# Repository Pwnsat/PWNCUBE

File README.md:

# PWNCUBE - The Vulnerable Satellite Hacking Platform for Learning Through Research

**A hardware-based CubeSat platform for aerospace cybersecurity research and training**, developed by PWNSAT in partnership with [ElectronicCats](https://github.com/ElectronicCats). PWNCUBE is a satellite design and vulnerability set onto real dual-core flight-computer hardware (Rockchip RV1106 — Cortex-A7 Linux + RISC-V RT-Thread), demonstrating that the same class of satellite command-and-control vulnerabilities reproduces across genuinely different hardware, not just one reference board.

Full documentation, architecture diagrams, and step-by-step guides live in the **[Wiki](../../wiki)**.

## Repository layout

| Folder | Contents |
|---|---|
| [`Firmware/`](Firmware/) | The complete RV1106 SDK source: dual-core boot (Cortex-A7 Linux + RISC-V RT-Thread), CCSDS Space Packet Protocol stack, radio/sensor/GPS drivers, build scripts. Clone-and-build (see [Getting Started](../../wiki/Getting-Started)). |
| [`Hardware/`](Hardware/) | KiCad schematics and PCB design files for the three physical boards (main/flight-computer, sensor, battery). |
| [`Case/`](Case/) | 3D-printable enclosure (STL + slicer project files). |

The 8 hardware-validated attack scripts (00–07, USB and real RF) live in a
companion `Attacks/` repository, published separately.

## What PWNCUBE demonstrates

Same protocol (CCSDS Space Packet Protocol), same command APIDs, same vulnerability classes as FlatSat — reproduced on real dual-core flight hardware instead of a single-MCU reference board:

- **No authentication** on any telecommand (thruster control, reset, firmware disclosure, mode changes)
- **No anti-replay protection** — a captured command can be resent verbatim and re-executed
- **A ground-station "auth" handshake** trivially forgeable with a static, hardcoded XOR key
- **A GPS subsystem** (real u-blox NEO-6M receiver) that trusts any injected fix with zero plausibility or rate-of-change checking
- **Plaintext telemetry by default** — no encryption on the downlink at all, unlike FlatSat's static-key AES-128
- **A memory-safety bug** (integer underflow in message reassembly) that crashes the flight computer's real-time core with a single malformed packet, permanently killing the internal command channel until a physical power-cycle

See the **[Attack Vectors](../../wiki/Attack-Vectors)** wiki page for the full walkthrough of all 8 attacks, with real hardware output for each.

## Quick start

```bash
git clone <this-repo-url> PWNCUBE-FIRMWARE
cd PWNCUBE-FIRMWARE/Firmware
# extract toolchain.tar.gz + rkbin.tar.gz from the v6 Release first — see below
./build.sh deps      # install host build dependencies (native Linux x86-64)
./build.sh            # produces output/images/update.img
```

On macOS, Windows, or if you'd rather not install packages on the host
directly, build inside Docker instead — see **[Getting Started](../../wiki/Getting-Started)**
for the full walkthrough (both paths), including flashing, which always
needs a real Linux x86-64 host or VM with USB passthrough regardless of how
you built.

## Note on repository size

This repository intentionally excludes two things present in the original SDK archive, both available as assets on the **[v6 Release](../../releases/tag/v6)**:

- **`toolchain/`** (ARM + RISC-V cross-compilers, ~2.6GB) — third-party, freely redistributable, just too large for a source repo.
- **`src/rkbin/`** (Rockchip's proprietary boot-stage binaries) — third-party, provided by ElectronicCats.

Everything else — kernel, U-Boot, the RT-Thread MCU firmware, all PWNSAT-authored application code — is included as source.

## Disclaimer

This project was created for educational purposes, to teach and learn aerospace cybersecurity. Neither PWNSAT nor Electronic Cats are responsible for how the knowledge, code, or tools hosted in this repository are used. Use only against hardware, firmware, or signal sources you own or are explicitly authorized to test.

## License

Firmware source: see [`Firmware/README.md`](Firmware/README.md#license) for the per-component breakdown (this SDK integrates code under several different open-source licenses). Attack scripts and this repository's own documentation: MIT unless noted otherwise.

## Related projects

- **[FlatSat](https://github.com/Pwnsat/FlatSat)** — the original single-MCU (RP2040) satellite security training platform this project ports from.
- **PWNSAT-C3** — the shared ground-station dashboard used to operate both FlatSat and PWNCUBE (separate repository).

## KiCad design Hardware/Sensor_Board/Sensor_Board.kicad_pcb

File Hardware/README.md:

# PWNCUBE hardware — KiCad schematics and PCB design files

Design files for the three physical boards that make up a PWNCUBE (see
[Hardware Anatomy](https://github.com/Pwnsat/PWNCUBE/wiki/Hardware-Anatomy)
in the wiki for how they connect and what runs on each).

| Folder | Board | Contains |
|---|---|---|
| `PWNSAT/` | Main / flight-computer board | RV1106 SoC, radios, USB selector, power supply |
| `Sensor_Board/` | Sensor board | BME280 + ICM-42670, sensor connectors |
| `Battery_Board/` | Power/battery board | Battery holder, USB, battery connector |

Each board folder is a self-contained KiCad project: `.kicad_pro` (project),
`.kicad_sch` (schematic sheets), `.kicad_pcb` (PCB layout), `.pretty/`
(custom footprint library), and `3D/` (3D models for parts used in that
board's layout, `.step`/`.stp`/`.igs`).

## Opening a project

Requires [KiCad](https://www.kicad.org/) (developed against KiCad 7/8).
Open the `.kicad_pro` file in each board's folder — schematic and PCB editors
are reachable from there.

## Generating manufacturing files (gerbers)

`electroniccats_pcb.kibot.yaml` and `electroniccats_sch.kibot.yaml` are
[KiBot](https://github.com/INTI-CMNB/KiBot) configs for JLCPCB-compatible
output (gerbers + drill files, schematic PDF). With KiBot installed:

```bash
kibot -c electroniccats_pcb.kibot.yaml -e <board>/<board>.kicad_sch -b <board>/<board>.kicad_pcb
```

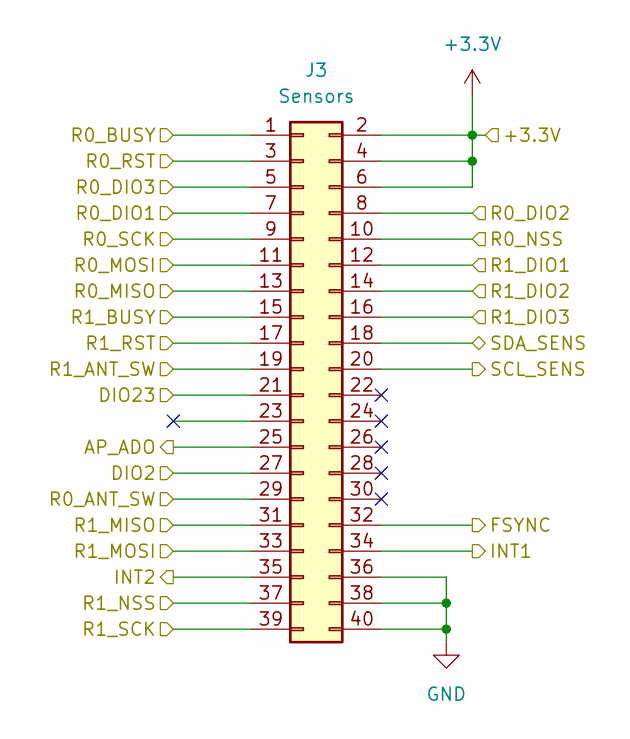
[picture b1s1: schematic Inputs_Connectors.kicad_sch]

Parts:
J3: Sensors; PinHeader_2x20_P2.54mm_Vertical; LCSC# C7501249

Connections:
+3.3V: J3.2, J3.4, J3.6; also elsewhere on the board
/Inputs_Connectors/AP_ADO: J3.25; also elsewhere on the board
/Inputs_Connectors/DIO2: J3.27; also elsewhere on the board
/Inputs_Connectors/DIO23: J3.21; also elsewhere on the board
/Inputs_Connectors/FSYNC: J3.32; also elsewhere on the board
/Inputs_Connectors/INT1: J3.34; also elsewhere on the board
/Inputs_Connectors/INT2: J3.35; also elsewhere on the board
/Inputs_Connectors/R0_ANT_SW: J3.29; also elsewhere on the board
/Inputs_Connectors/R0_BUSY: J3.1; also elsewhere on the board
/Inputs_Connectors/R0_DIO1: J3.7; also elsewhere on the board
/Inputs_Connectors/R0_DIO3: J3.5; also elsewhere on the board
/Inputs_Connectors/R0_MISO: J3.13; also elsewhere on the board
/Inputs_Connectors/R0_MOSI: J3.11; also elsewhere on the board
/Inputs_Connectors/R0_NSS: J3.10; also elsewhere on the board
/Inputs_Connectors/R0_RST: J3.3; also elsewhere on the board
/Inputs_Connectors/R0_SCK: J3.9; also elsewhere on the board
/Inputs_Connectors/R1_ANT_SW: J3.19; also elsewhere on the board
/Inputs_Connectors/R1_BUSY: J3.15; also elsewhere on the board
/Inputs_Connectors/R1_DIO1: J3.12; also elsewhere on the board
/Inputs_Connectors/R1_DIO3: J3.16; also elsewhere on the board
/Inputs_Connectors/R1_MISO: J3.31; also elsewhere on the board
/Inputs_Connectors/R1_MOSI: J3.33; also elsewhere on the board
/Inputs_Connectors/R1_NSS: J3.37; also elsewhere on the board
/Inputs_Connectors/R1_RST: J3.17; also elsewhere on the board
/Inputs_Connectors/R1_SCK: J3.39; also elsewhere on the board
/Inputs_Connectors/SCL_SENS: J3.20; also elsewhere on the board
/Inputs_Connectors/SDA_SENS: J3.18; also elsewhere on the board
/Sensors/R0_DIO2: J3.8; also elsewhere on the board
/Sensors/R1_DIO2: J3.14; also elsewhere on the board
GND: J3.36, J3.38, J3.40; also elsewhere on the board

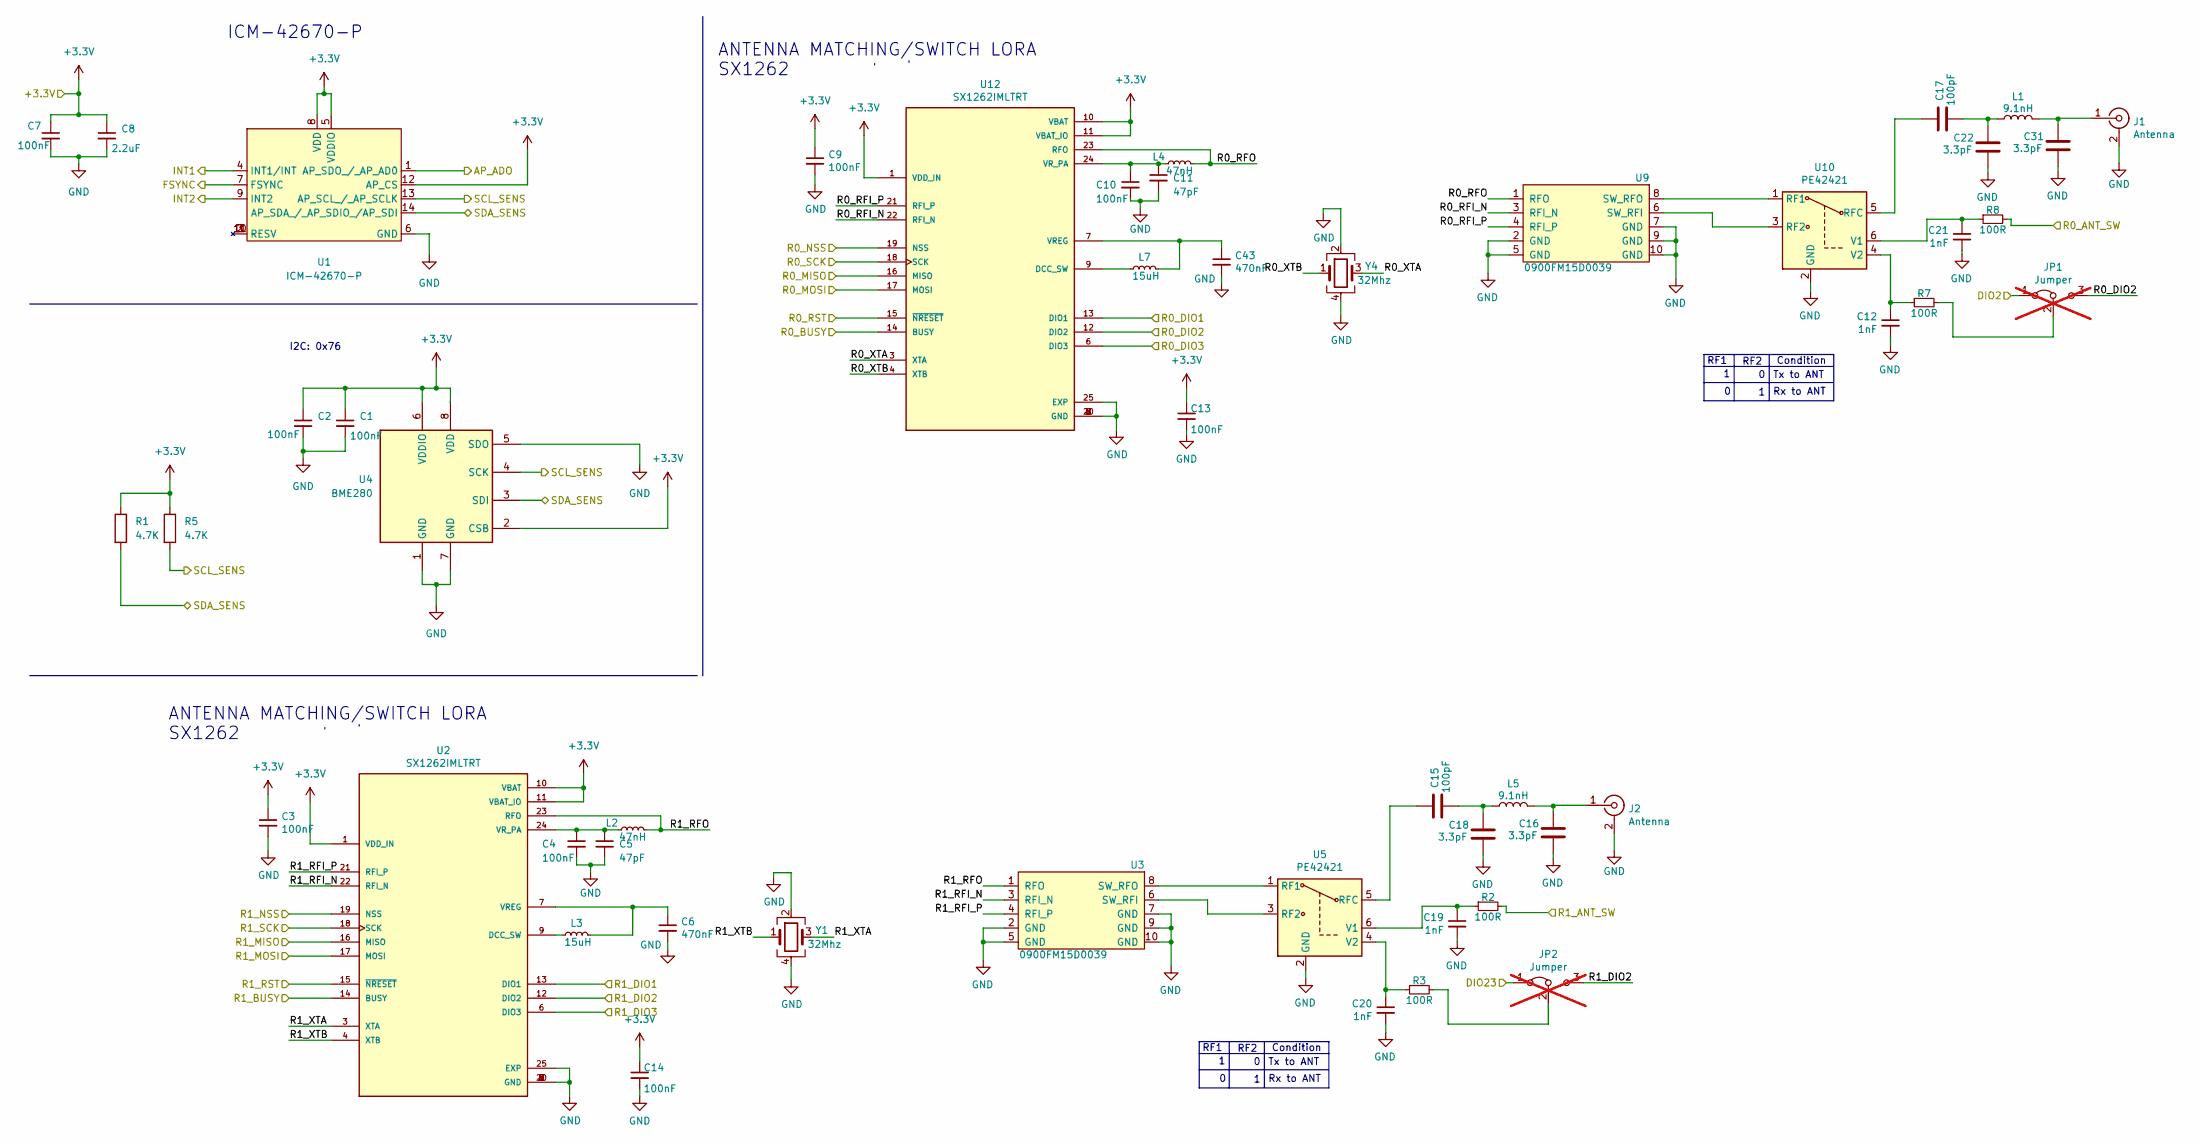
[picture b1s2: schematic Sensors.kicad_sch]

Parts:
C1, C2, C3, C4, C7, C9, C10, C13, C14: 100nF; C_0402_1005Metric; LCSC# C56392
C5, C11: 47pF; C_0402_1005Metric; LCSC# C437519
C6, C43: 470nF; C_0402_1005Metric; LCSC# C47339
C8: 2.2uF; C_0402_1005Metric; LCSC# C170151
C12, C19, C20, C21: 1nF; C_0402_1005Metric; LCSC# C76947
C15, C17: 100pF; C_0402_1005Metric; LCSC# C541374
C16, C18, C22, C31: 3.3pF; C_0402_1005Metric; LCSC# C1565
J1, J2: Antenna; SMA_EDGE; LCSC# C530661
JP1, JP2: Jumper; SolderJumper-3_P1.3mm_Bridged12_RoundedPad1.0x1.5mm_NumberL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; LCSC# ---; not fitted
L1, L5: 9.1nH; L_0603_1608Metric; LCSC# C395094
L2, L4: 47nH; L_0603_1608Metric; LCSC# C578001
L3, L7: 15uH; L_0603_1608Metric; LCSC# C2885870
R1, R5: 4.7K; R_0402_1005Metric_Pad0.72x0.64mm_HandSolder; LCSC# C400631
R2, R3, R7, R8: 100R; R_0402_1005Metric; LCSC# C25076
U1: ICM-42670-P; LGA-14_3x2.5mm_P0.5mm_LayoutBorder3x4y; LCSC# C3288646
U2, U12: SX1262IMLTRT; QFN-24-1EP_4x4mm_P0.5mm_EP2.65x2.65mm; Mouser# 947-SX1262IMLTRT
U3, U9: 0900FM15D0039; 0900FM15D0039E; Mouser# 609-0900FM15D0039E
U4: BME280; Bosch_LGA-8_2.5x2.5mm_P0.65mm_ClockwisePinNumbering; LCSC# C92489
U5, U10: PE42421; SOT-363_SC-70-6; Mouser# 81-PE42421SCAA-Z; LCSC# C470893
Y1, Y4: 32Mhz; Crystal_SMD_2520-4Pin_2.5x2.0mm; LCSC# C255969

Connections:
+3.3V: C1.1, C2.1, C3.1, C7.1, C8.1, C9.1, C13.1, C14.1, R1.1, R5.1, U1.5 (VDDIO), U1.8 (VDD), U1.12 (AP_CS), U2.1 (VDD_IN), U2.10 (VBAT), U2.11 (VBAT_IO), U4.2 (CSB), U4.6 (VDDIO), U4.8 (VDD), U12.1 (VDD_IN), U12.10 (VBAT), U12.11 (VBAT_IO); also elsewhere on the board
/Inputs_Connectors/AP_ADO: U1.1 (AP_SDO_/_AP_AD0); also elsewhere on the board
/Inputs_Connectors/DIO2: JP1.1 (A); also elsewhere on the board
/Inputs_Connectors/DIO23: JP2.1 (A); also elsewhere on the board
/Inputs_Connectors/FSYNC: U1.7 (FSYNC); also elsewhere on the board
/Inputs_Connectors/INT1: U1.4 (INT1/INT); also elsewhere on the board
/Inputs_Connectors/INT2: U1.9 (INT2); also elsewhere on the board
/Inputs_Connectors/R0_ANT_SW: R8.2; also elsewhere on the board
/Inputs_Connectors/R0_BUSY: U12.14 (BUSY); also elsewhere on the board
/Inputs_Connectors/R0_DIO1: U12.13 (DIO1); also elsewhere on the board
/Inputs_Connectors/R0_DIO3: U12.6 (DIO3); also elsewhere on the board
/Inputs_Connectors/R0_MISO: U12.16 (MISO); also elsewhere on the board
/Inputs_Connectors/R0_MOSI: U12.17 (MOSI); also elsewhere on the board
/Inputs_Connectors/R0_NSS: U12.19 (NSS); also elsewhere on the board
/Inputs_Connectors/R0_RST: U12.15 (~NRESET); also elsewhere on the board
/Inputs_Connectors/R0_SCK: U12.18 (SCK); also elsewhere on the board
/Inputs_Connectors/R1_ANT_SW: R2.2; also elsewhere on the board
/Inputs_Connectors/R1_BUSY: U2.14 (BUSY); also elsewhere on the board
/Inputs_Connectors/R1_DIO1: U2.13 (DIO1); also elsewhere on the board
/Inputs_Connectors/R1_DIO3: U2.6 (DIO3); also elsewhere on the board
/Inputs_Connectors/R1_MISO: U2.16 (MISO); also elsewhere on the board
/Inputs_Connectors/R1_MOSI: U2.17 (MOSI); also elsewhere on the board
/Inputs_Connectors/R1_NSS: U2.19 (NSS); also elsewhere on the board
/Inputs_Connectors/R1_RST: U2.15 (~NRESET); also elsewhere on the board
/Inputs_Connectors/R1_SCK: U2.18 (SCK); also elsewhere on the board
/Inputs_Connectors/SCL_SENS: R5.2, U1.13 (AP_SCL_/_AP_SCLK), U4.4 (SCK); also elsewhere on the board
/Inputs_Connectors/SDA_SENS: R1.2, U1.14 (AP_SDA_/_AP_SDIO_/AP_SDI), U4.3 (SDI); also elsewhere on the board
/Sensors/R0_DIO2: JP1.3 (B), U12.12 (DIO2); also elsewhere on the board
/Sensors/R0_RFI_N: U9.3 (RFI_N), U12.22 (RFI_N)
/Sensors/R0_RFI_P: U9.4 (RFI_P), U12.21 (RFI_P)
/Sensors/R0_RFO: L4.2, U9.1 (RFO), U12.23 (RFO)
/Sensors/R0_XTA: U12.3 (XTA), Y4.3
/Sensors/R0_XTB: U12.4 (XTB), Y4.1
/Sensors/R1_DIO2: JP2.3 (B), U2.12 (DIO2); also elsewhere on the board
/Sensors/R1_RFI_N: U2.22 (RFI_N), U3.3 (RFI_N)
/Sensors/R1_RFI_P: U2.21 (RFI_P), U3.4 (RFI_P)
/Sensors/R1_RFO: L2.2, U2.23 (RFO), U3.1 (RFO)
/Sensors/R1_XTA: U2.3 (XTA), Y1.3
/Sensors/R1_XTB: U2.4 (XTB), Y1.1
GND: C1.2, C2.2, C3.2, C4.2, C5.2, C6.2, C7.2, C8.2, C9.2, C10.2, C11.2, C12.2, C13.2, C14.2, C16.2, C18.2, C19.2, C20.2, C21.2, C22.2, C31.2, C43.2, J1.2 (Ext), J2.2 (Ext), U1.6 (GND), U2.2 (GND), U2.5 (GND), U2.8 (GND), U2.20 (GND), U2.25 (EXP), U3.2 (GND), U3.5 (GND), U3.7 (GND), U3.9 (GND), U3.10 (GND), U4.1 (GND), U4.5 (SDO), U4.7 (GND), U5.2 (GND), U9.2 (GND), U9.5 (GND), U9.7 (GND), U9.9 (GND), U9.10 (GND), U10.2 (GND), U12.2 (GND), U12.5 (GND), U12.8 (GND), U12.20 (GND), U12.25 (EXP), Y1.2, Y1.4, Y4.2, Y4.4; also elsewhere on the board
unnamed: C15.2, C18.1, L5.2
unnamed: C17.2, C22.1, L1.2
unnamed: C31.1, J1.1 (In), L1.1
unnamed: C16.1, J2.1 (In), L5.1
unnamed: JP1.2 (C), R7.2
unnamed: JP2.2 (C), R3.2
unnamed: L3.1, U2.9 (DCC_SW)
unnamed: C6.1, L3.2, U2.7 (VREG)
unnamed: C4.1, C5.1, L2.1, U2.24 (VR_PA)
unnamed: U3.6 (SW_RFI), U5.3 (RF2)
unnamed: U3.8 (SW_RFO), U5.1 (RF1)
unnamed: C15.1, U5.5 (RFC)
unnamed: C19.1, R2.1, U5.6 (V1)
unnamed: C20.1, R3.1, U5.4 (V2)
unnamed: U9.8 (SW_RFO), U10.1 (RF1)
unnamed: U9.6 (SW_RFI), U10.3 (RF2)
unnamed: C17.1, U10.5 (RFC)
unnamed: C21.1, R8.1, U10.6 (V1)
unnamed: C12.1, R7.1, U10.4 (V2)
unnamed: L7.1, U12.9 (DCC_SW)
unnamed: C43.1, L7.2, U12.7 (VREG)
unnamed: C10.1, C11.1, L4.1, U12.24 (VR_PA)

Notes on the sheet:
ANTENNA MATCHING/SWITCH LORA
Condition
Tx to ANT
SX1262
RF2
RF1
Rx to ANT
I2C: 0x76
ICM-42670-P

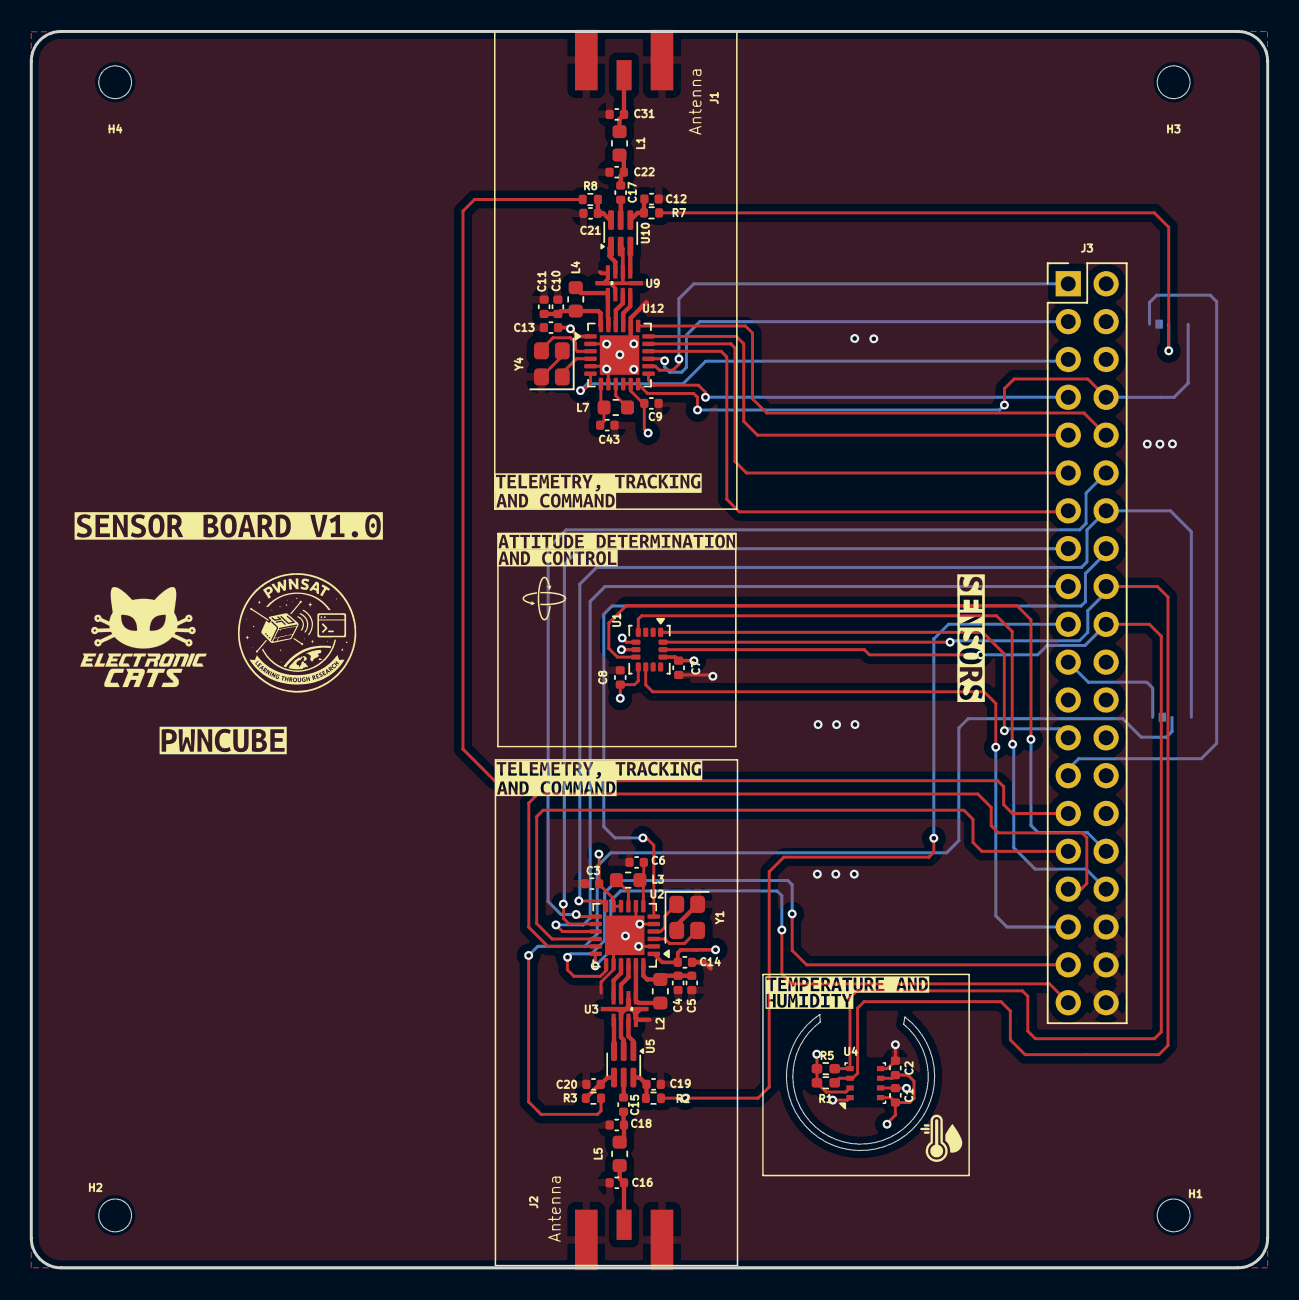
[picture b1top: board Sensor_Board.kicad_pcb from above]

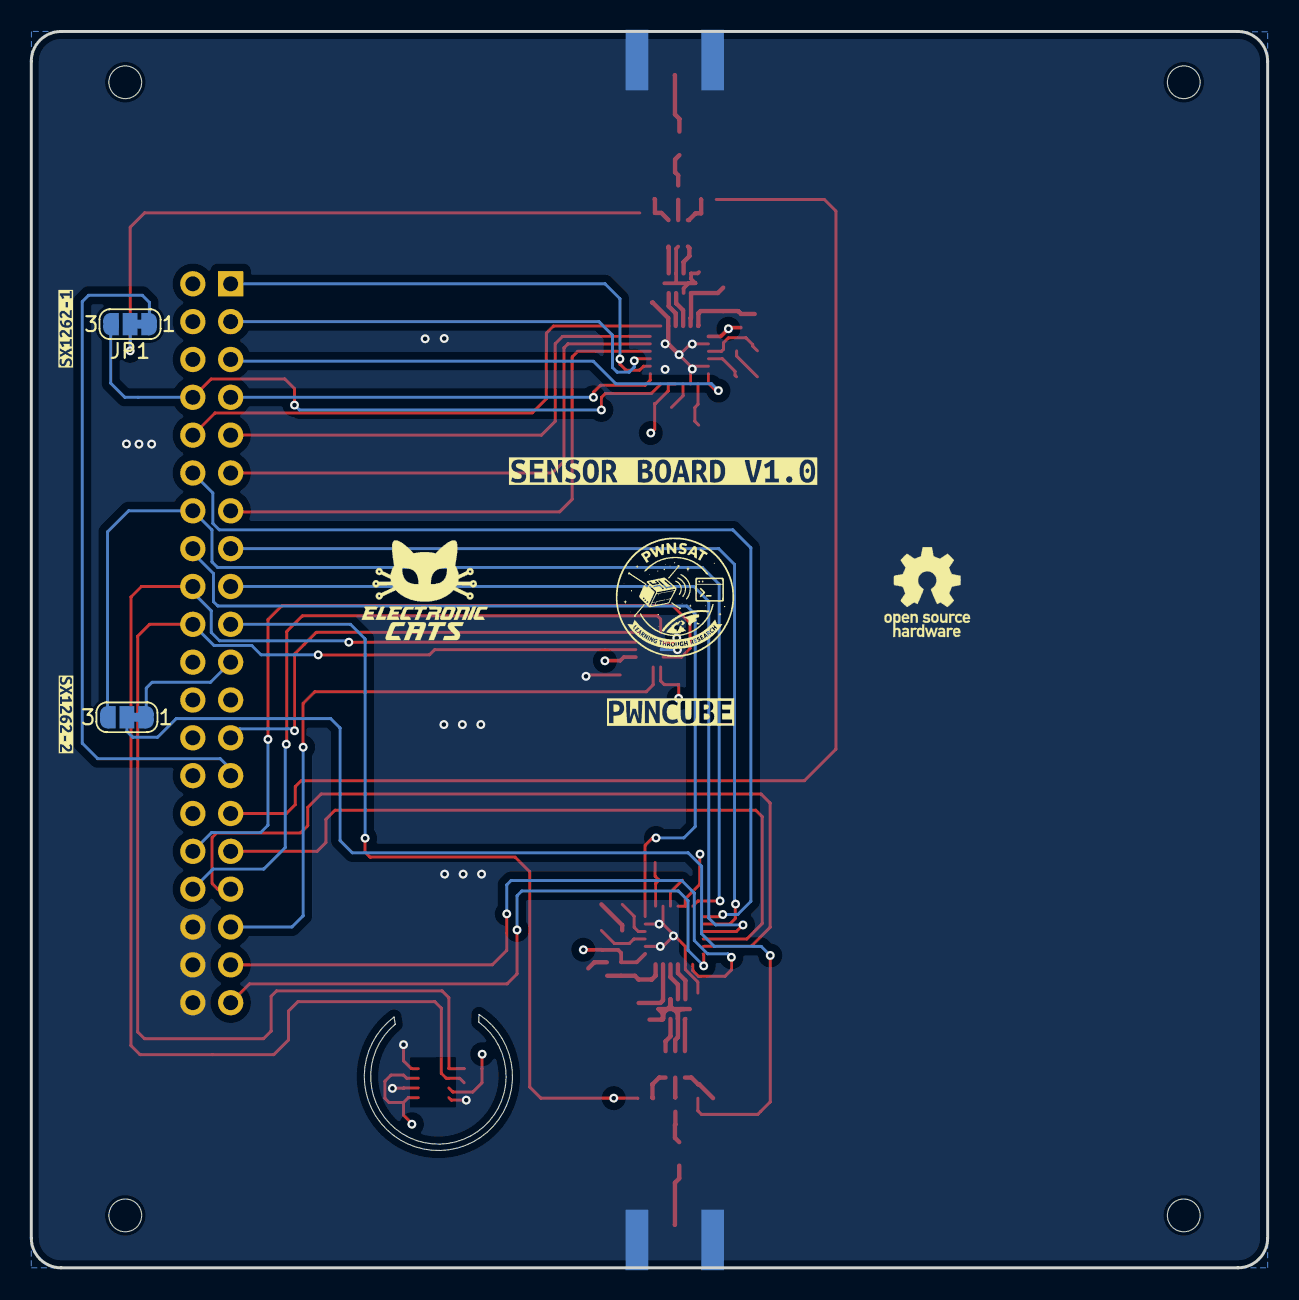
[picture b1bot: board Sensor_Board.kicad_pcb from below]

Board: 4 copper layers, 83.0 x 83.0 mm, 70 parts (6 on the bottom side), 62 nets.

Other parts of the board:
H1, H2, H3, H4: MountingHole; MountingHole_2.2mm_M2
kibuzzard-69860F52: G***; kibuzzard-69860F52
kibuzzard-69860F65: G***; kibuzzard-69860F65
kibuzzard-69866AEC: G***; kibuzzard-69866AEC
kibuzzard-69866B09: G***; kibuzzard-69866B09
kibuzzard-698518BF, kibuzzard-698518BF#2: G***; kibuzzard-698518BF
kibuzzard-698518EC, kibuzzard-698518EC#2: G***; kibuzzard-698518EC
kibuzzard-698668F8: G***; kibuzzard-698668F8
kibuzzard-698669D4, kibuzzard-698669D4#2: G***; kibuzzard-698669D4
kibuzzard-698669E3, kibuzzard-698669E3#2: G***; kibuzzard-698669E3
kibuzzard-6985197E: G***; kibuzzard-6985197E
kibuzzard-69866904: G***; kibuzzard-69866904

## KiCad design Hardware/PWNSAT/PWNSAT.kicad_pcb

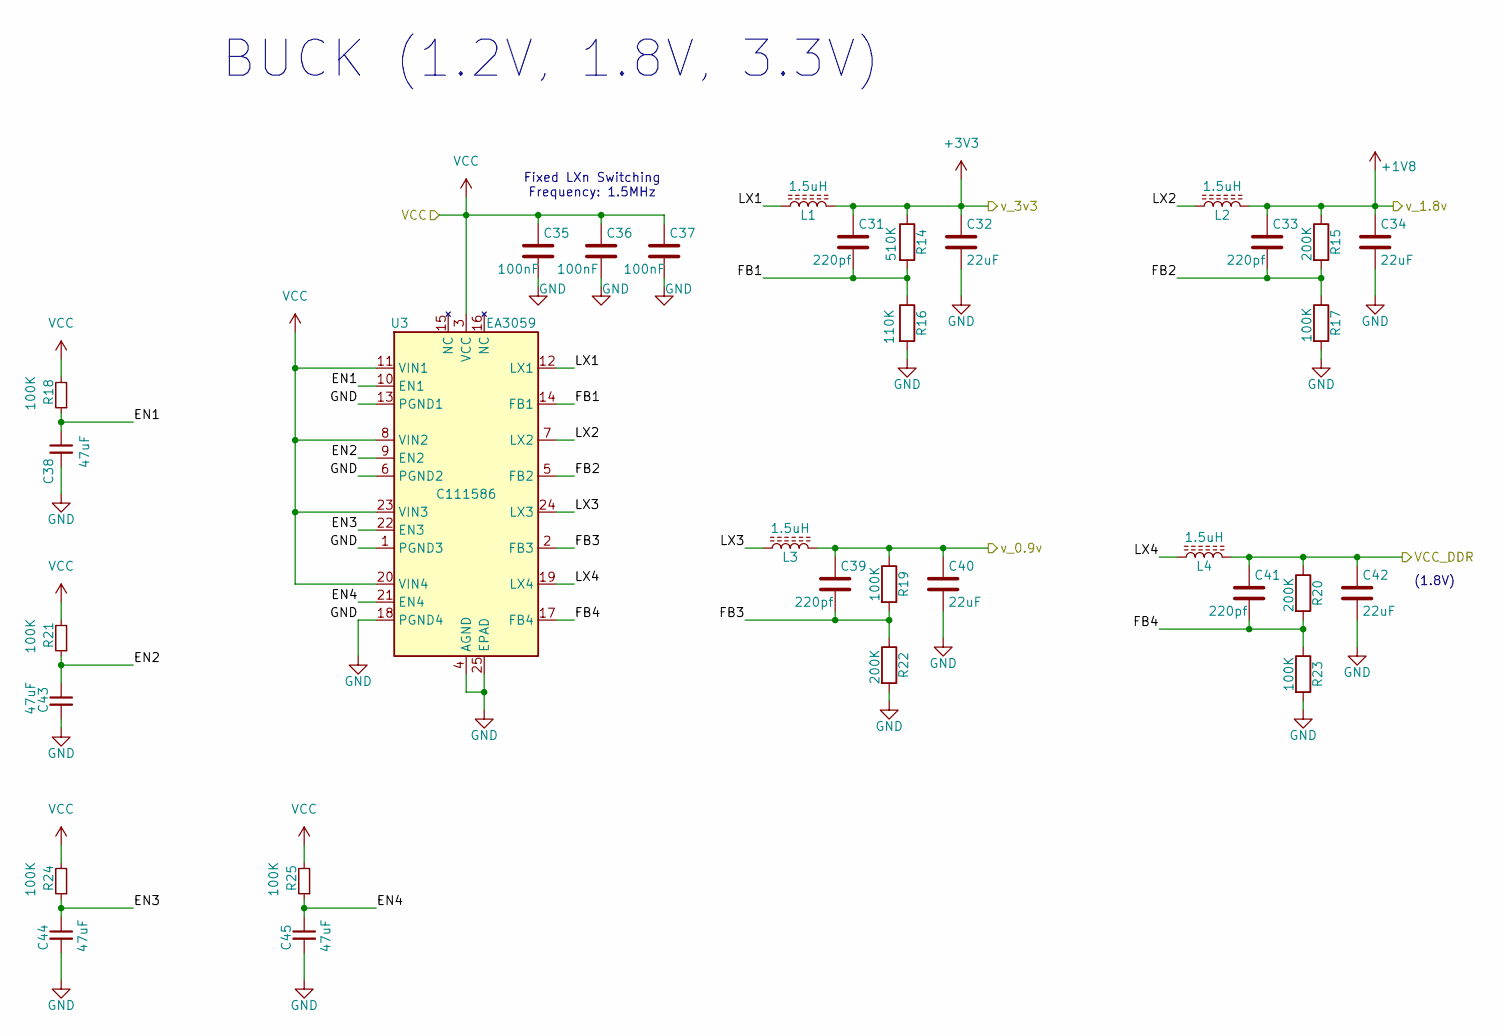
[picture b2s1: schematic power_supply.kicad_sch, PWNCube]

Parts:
C31, C33, C39, C41: 220pf; C_0402_1005Metric_Pad0.74x0.62mm_HandSolder; LCSC# C327000
C32, C34, C40, C42: 22uF; C_0402_1005Metric; LCSC# C415703
C35, C36, C37: 100nF; C_0402_1005Metric_Pad0.74x0.62mm_HandSolder; LCSC# C56392
C38, C43, C44, C45: 47uF; C_0603_1608Metric; LCSC# C140782
L1, L2, L3, L4: 1.5uH; L_1008_2520Metric; LCSC# C7427193
R14: 510K; R_0402_1005Metric_Pad0.72x0.64mm_HandSolder; LCSC# C365024
R15, R20, R22: 200K; R_0402_1005Metric_Pad0.72x0.64mm_HandSolder; LCSC# C364966
R16: 110K; R_0402_1005Metric_Pad0.72x0.64mm_HandSolder; LCSC# C854086
R17, R18, R19, R21, R23, R24, R25: 100K; R_0402_1005Metric_Pad0.72x0.64mm_HandSolder; LCSC# C844674
U3: EA3059; VQFN-24-1EP_4x4mm_P0.5mm_EP2.5x2.5mm; LCSC# C111586

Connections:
+1V8: C33.1, C34.1, L2.2, R15.1; also elsewhere on the board
+3V3: C31.1, C32.1, L1.2, R14.1; also elsewhere on the board
/core/VCC_DDR: C41.1, C42.1, L4.2, R20.1; also elsewhere on the board
/core/VDD_ARM: C39.1, C40.1, L3.2, R19.1; also elsewhere on the board
/power_supply/EN1: C38.1, R18.1, U3.10 (EN1)
/power_supply/EN2: C43.1, R21.1, U3.9 (EN2)
/power_supply/EN3: C44.1, R24.1, U3.22 (EN3)
/power_supply/EN4: C45.1, R25.1, U3.21 (EN4)
/power_supply/FB1: C31.2, R14.2, R16.1, U3.14 (FB1)
/power_supply/FB2: C33.2, R15.2, R17.1, U3.5 (FB2)
/power_supply/FB3: C39.2, R19.2, R22.1, U3.2 (FB3)
/power_supply/FB4: C41.2, R20.2, R23.1, U3.17 (FB4)
/power_supply/LX1: L1.1, U3.12 (LX1)
/power_supply/LX2: L2.1, U3.7 (LX2)
/power_supply/LX3: L3.1, U3.24 (LX3)
/power_supply/LX4: L4.1, U3.19 (LX4)
GND: C32.2, C34.2, C35.2, C36.2, C37.2, C38.2, C40.2, C42.2, C43.2, C44.2, C45.2, R16.2, R17.2, R22.2, R23.2, U3.1 (PGND3), U3.4 (AGND), U3.6 (PGND2), U3.13 (PGND1), U3.18 (PGND4), U3.25 (EPAD); also elsewhere on the board
VCC: C35.1, C36.1, C37.1, R18.2, R21.2, R24.2, R25.2, U3.3 (VCC), U3.8 (VIN2), U3.11 (VIN1), U3.20 (VIN4), U3.23 (VIN3); also elsewhere on the board

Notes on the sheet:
BUCK (1.2V, 1.8V, 3.3V)
Fixed LXn Switching Frequency: 1.5MHz
(1.8V)

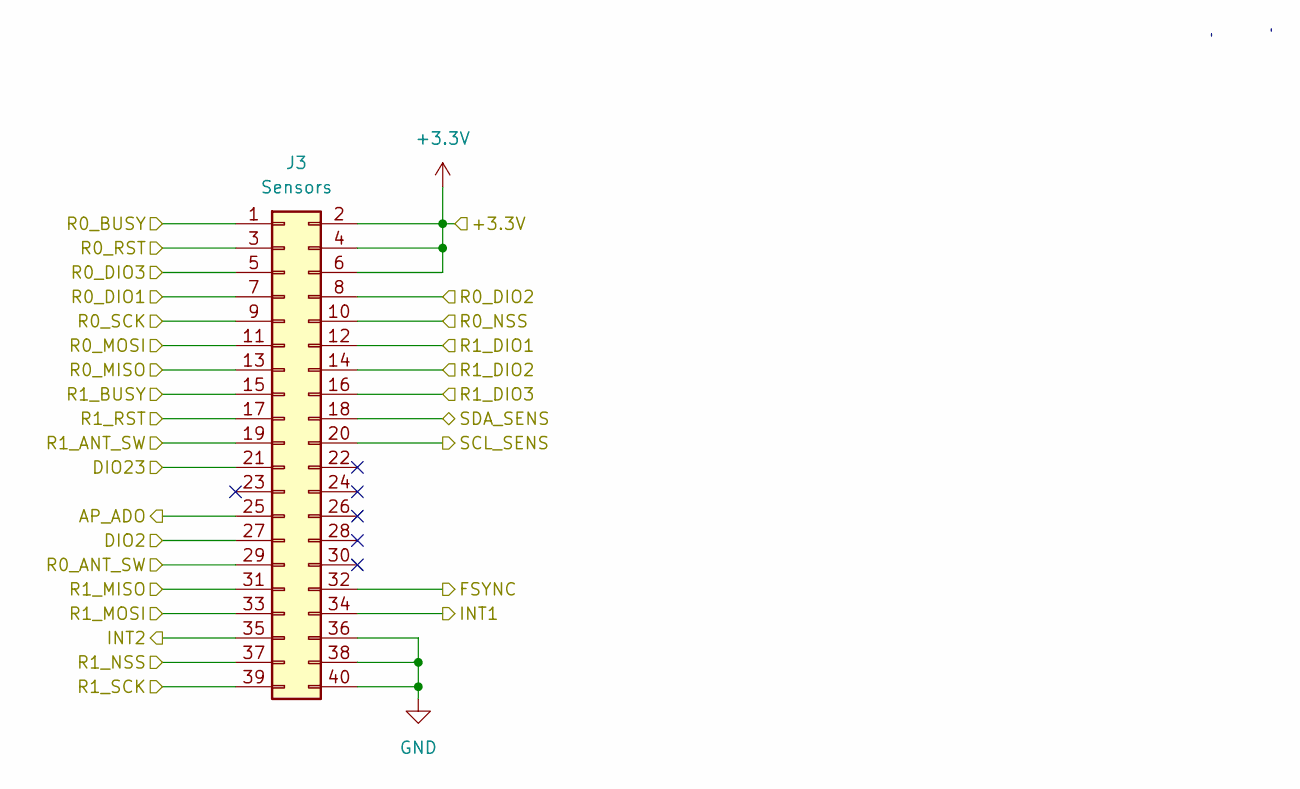
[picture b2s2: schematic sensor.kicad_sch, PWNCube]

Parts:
J3: Sensors; PinHeader_2x20_P2.54mm_Vertical; LCSC# C7501249

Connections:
+3.3V: J3.2, J3.4, J3.6; also elsewhere on the board
/Sensor/AP_ADO: J3.25; also elsewhere on the board
/Sensor/DIO2: J3.27; also elsewhere on the board
/Sensor/DIO23: J3.21; also elsewhere on the board
/Sensor/FSYNC: J3.32; also elsewhere on the board
/Sensor/INT1: J3.34; also elsewhere on the board
/Sensor/INT2: J3.35; also elsewhere on the board
/Sensor/R0_ANT_SW: J3.29; also elsewhere on the board
/Sensor/R0_BUSY: J3.1; also elsewhere on the board
/Sensor/R0_DIO1: J3.7; also elsewhere on the board
/Sensor/R0_DIO2: J3.8; also elsewhere on the board
/Sensor/R0_DIO3: J3.5; also elsewhere on the board
/Sensor/R0_MISO: J3.13; also elsewhere on the board
/Sensor/R0_MOSI: J3.11; also elsewhere on the board
/Sensor/R0_NSS: J3.10; also elsewhere on the board
/Sensor/R0_RST: J3.3; also elsewhere on the board
/Sensor/R0_SCK: J3.9; also elsewhere on the board
/Sensor/R1_ANT_SW: J3.19; also elsewhere on the board
/Sensor/R1_BUSY: J3.15; also elsewhere on the board
/Sensor/R1_DIO1: J3.12; also elsewhere on the board
/Sensor/R1_DIO2: J3.14; also elsewhere on the board
/Sensor/R1_DIO3: J3.16; also elsewhere on the board
/Sensor/R1_MISO: J3.31; also elsewhere on the board
/Sensor/R1_MOSI: J3.33; also elsewhere on the board
/Sensor/R1_NSS: J3.37; also elsewhere on the board
/Sensor/R1_RST: J3.17; also elsewhere on the board
/Sensor/R1_SCK: J3.39; also elsewhere on the board
/Sensor/SCL_SENS: J3.20; also elsewhere on the board
/Sensor/SDA_SENS: J3.18; also elsewhere on the board
GND: J3.36, J3.38, J3.40; also elsewhere on the board

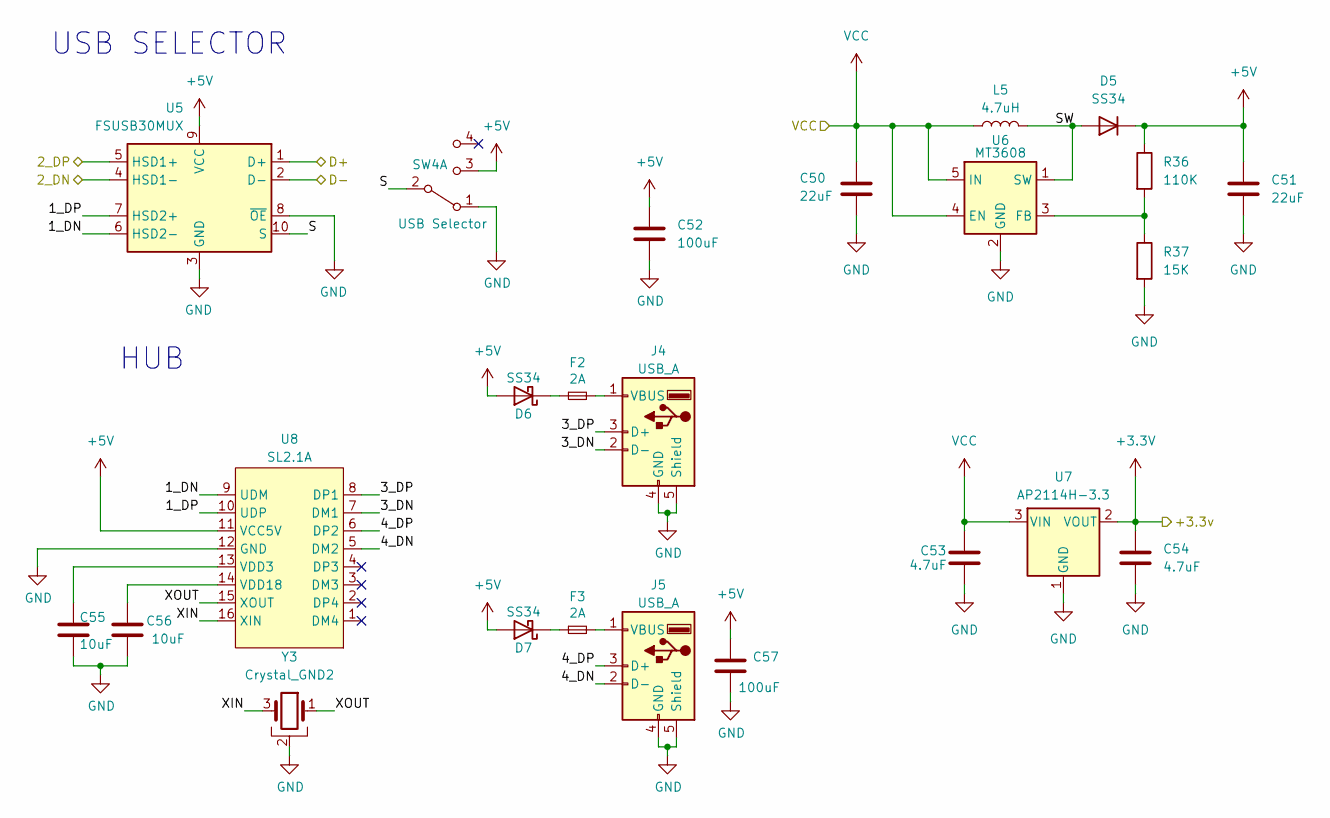
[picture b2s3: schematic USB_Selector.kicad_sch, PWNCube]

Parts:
C50, C51: 22uF; C_0402_1005Metric; LCSC# C415703
C52, C57: 100uF; C_0805_2012Metric; LCSC# C141660
C53, C54: 4.7uF; C_0402_1005Metric; LCSC# C368809
C55, C56: 10uF; C_0603_1608Metric; LCSC# C96446
D5, D6, D7: SS34; D_SMA; LCSC# C908680
F2, F3: 2A; Fuse_0603_1608Metric; LCSC# C41380229
J4, J5: USB_A; USB_A_Connfly_DS1095; LCSC# C2345
L5: 4.7uH; LQH5BPN; LCSC# C520334
R36: 110K; R_0603_1608Metric; LCSC# C326736
R37: 15K; R_0603_1608Metric; LCSC# C2989599
SW4: USB Selector; SW_Slide_SPDT_Angled_CK_OS102011MA1Q; LCSC# C393937
U5: FSUSB30MUX; IC_FSUSB42UMX; LCSC# C42370490
U6: MT3608; SOT-23-6; LCSC# C2932326
U7: AP2114H-3.3; SOT-223-3_TabPin2; LCSC# C150716
U8: SL2.1A; SO-16_3.9x9.9mm_P1.27mm; LCSC# C192893
Y3: Crystal_GND2; Crystal_SMD_3225-4Pin_3.2x2.5mm; LCSC# C133334

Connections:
+3.3V: C54.1, U7.2 (VOUT); also elsewhere on the board
+5V: C51.1, C52.1, C57.1, D5.1 (K), D6.2 (A), D7.2 (A), R36.1, SW4.3 (C), U5.9 (VCC), U8.11 (VCC5V)
/Source_Connector/2_DN: U5.4 (HSD1-); also elsewhere on the board
/Source_Connector/2_DP: U5.5 (HSD1+); also elsewhere on the board
/USB_Selector/1_DN: U5.6 (HSD2-), U8.9 (UDM)
/USB_Selector/1_DP: U5.7 (HSD2+), U8.10 (UDP)
/USB_Selector/3_DN: J4.2 (D-), U8.7 (DM1)
/USB_Selector/3_DP: J4.3 (D+), U8.8 (DP1)
/USB_Selector/4_DN: J5.2 (D-), U8.5 (DM2)
/USB_Selector/4_DP: J5.3 (D+), U8.6 (DP2)
/USB_Selector/D+: U5.1 (D+); also elsewhere on the board
/USB_Selector/D-: U5.2 (D-); also elsewhere on the board
/USB_Selector/S: SW4.2 (B), U5.10 (S)
/USB_Selector/SW: D5.2 (A), L5.2, U6.1 (SW)
/USB_Selector/XIN: U8.16 (XIN), Y3.3
/USB_Selector/XOUT: U8.15 (XOUT), Y3.1
GND: C50.2, C51.2, C52.2, C53.2, C54.2, C55.2, C56.1, C57.2, J4.4 (GND), J4.5 (Shield), J5.4 (GND), J5.5 (Shield), R37.2, SW4.1 (A), U5.3 (GND), U5.8 (~OE), U6.2 (GND), U7.1 (GND), U8.12 (GND), Y3.2, Y3.4; also elsewhere on the board
unnamed: D6.1 (K), F2.1
unnamed: D7.1 (K), F3.1
unnamed: F2.2, J4.1 (VBUS)
unnamed: F3.2, J5.1 (VBUS)
unnamed: R36.2, R37.1, U6.3 (FB)
unnamed: C55.1, U8.13 (VDD3)
unnamed: C56.2, U8.14 (VDD18)
VCC: C50.1, C53.1, L5.1, U6.4 (EN), U6.5 (IN), U7.3 (VIN); also elsewhere on the board

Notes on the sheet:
HUB
USB SELECTOR

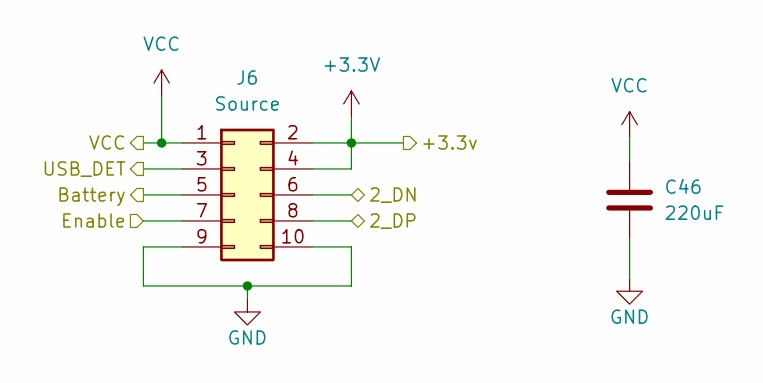
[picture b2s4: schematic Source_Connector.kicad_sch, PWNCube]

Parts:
C46: 220uF; C_1206_3216Metric
J6: Source; PinHeader_2x05_P2.54mm_Vertical; LCSC# C7501191

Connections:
+3.3V: J6.2, J6.4; also elsewhere on the board
/Source_Connector/2_DN: J6.6; also elsewhere on the board
/Source_Connector/2_DP: J6.8; also elsewhere on the board
/Source_Connector/Battery: J6.5; also elsewhere on the board
/Source_Connector/Enable: J6.7; also elsewhere on the board
/Source_Connector/USB_DET: J6.3; also elsewhere on the board
GND: C46.2, J6.9, J6.10; also elsewhere on the board
VCC: C46.1, J6.1; also elsewhere on the board

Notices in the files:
Firmware/dts/rv1106-sdk-ipc.dtsi:
SPDX-License-Identifier: (GPL-2.0+ OR MIT)
Copyright (c) 2022 Rockchip Electronics Co., Ltd.
